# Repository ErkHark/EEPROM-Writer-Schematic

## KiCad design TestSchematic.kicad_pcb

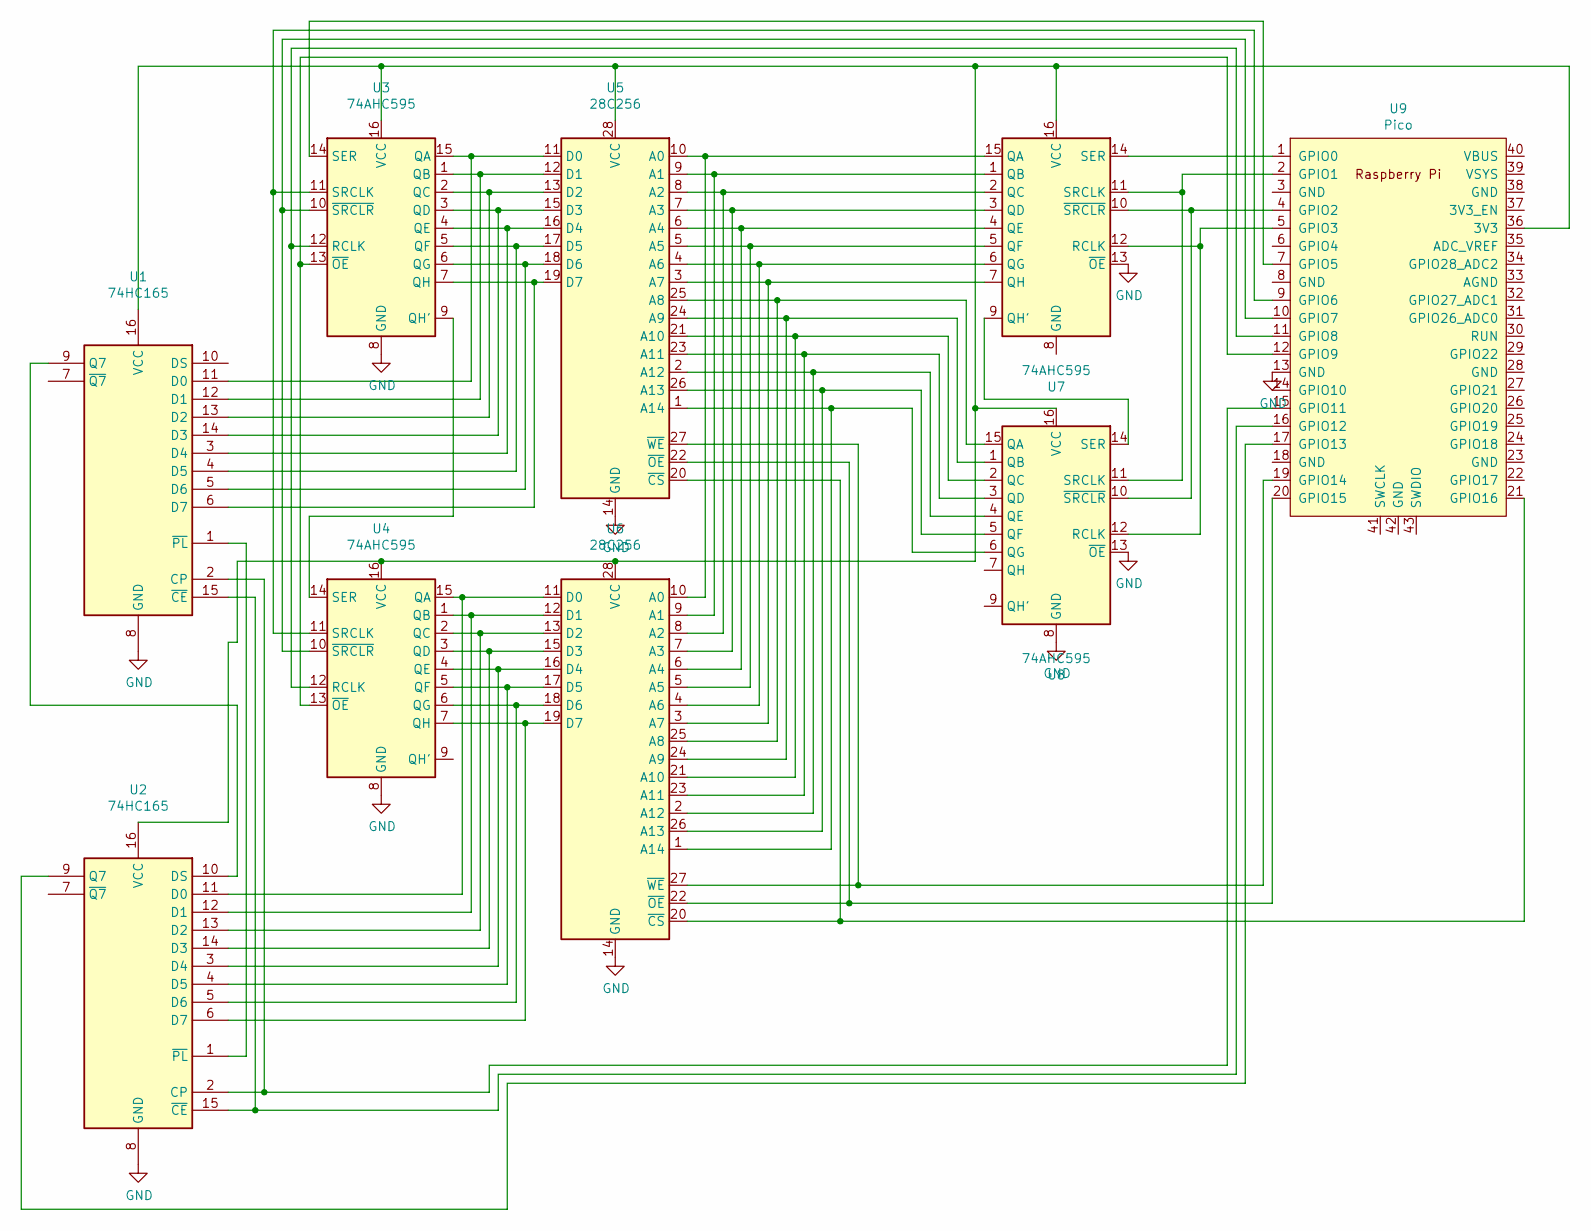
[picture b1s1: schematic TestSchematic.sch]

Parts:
U1, U2: 74HC165; DIP-16_W7.62mm_Socket
U3, U4, U7, U8: 74AHC595; DIP-16_W7.62mm_Socket
U5, U6: 28C256; DIP-28_W15.24mm
U9: Pico; RPi_Pico_SMD_TH

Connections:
unnamed: U1.1 (~PL), U2.1 (~PL)
unnamed: U1.2 (CP), U2.2 (CP), U9.15 (GPIO11)
unnamed: U1.3 (D4), U3.4 (QE), U5.16 (D4)
unnamed: U1.4 (D5), U3.5 (QF), U5.17 (D5)
unnamed: U1.5 (D6), U3.6 (QG), U5.18 (D6)
unnamed: U1.6 (D7), U3.7 (QH), U5.19 (D7)
unnamed: U1.8 (GND), U2.8 (GND), U3.8 (GND), U4.8 (GND), U5.14 (GND), U6.14 (GND), U7.8 (GND), U7.13 (~OE), U8.8 (GND), U8.13 (~OE), U9.13 (GND)
unnamed: U1.9 (Q7), U2.10 (DS)
unnamed: U1.11 (D0), U3.15 (QA), U5.11 (D0)
unnamed: U1.12 (D1), U3.1 (QB), U5.12 (D1)
unnamed: U1.13 (D2), U3.2 (QC), U5.13 (D2)
unnamed: U1.14 (D3), U3.3 (QD), U5.15 (D3)
unnamed: U1.15 (~CE), U2.15 (~CE), U9.16 (GPIO12)
unnamed: U1.16 (VCC), U2.16 (VCC), U3.16 (VCC), U4.16 (VCC), U5.28 (VCC), U6.28 (VCC), U7.16 (VCC), U8.16 (VCC), U9.36 (3V3)
unnamed: U2.3 (D4), U4.4 (QE), U6.16 (D4)
unnamed: U2.4 (D5), U4.5 (QF), U6.17 (D5)
unnamed: U2.5 (D6), U4.6 (QG), U6.18 (D6)
unnamed: U2.6 (D7), U4.7 (QH), U6.19 (D7)
unnamed: U2.9 (Q7), U9.17 (GPIO13)
unnamed: U2.11 (D0), U4.15 (QA), U6.11 (D0)
unnamed: U2.12 (D1), U4.1 (QB), U6.12 (D1)
unnamed: U2.13 (D2), U4.2 (QC), U6.13 (D2)
unnamed: U2.14 (D3), U4.3 (QD), U6.15 (D3)
unnamed: U3.9 (QH'), U4.14 (SER)
unnamed: U3.10 (~SRCLR), U4.10 (~SRCLR), U9.10 (GPIO7)
unnamed: U3.11 (SRCLK), U4.11 (SRCLK), U9.9 (GPIO6)
unnamed: U3.12 (RCLK), U4.12 (RCLK), U9.11 (GPIO8)
unnamed: U3.13 (~OE), U4.13 (~OE), U9.12 (GPIO9)
unnamed: U3.14 (SER), U9.7 (GPIO5)
unnamed: U5.1 (A14), U6.1 (A14), U8.6 (QG)
unnamed: U5.2 (A12), U6.2 (A12), U8.4 (QE)
unnamed: U5.3 (A7), U6.3 (A7), U7.7 (QH)
unnamed: U5.4 (A6), U6.4 (A6), U7.6 (QG)
unnamed: U5.5 (A5), U6.5 (A5), U7.5 (QF)
unnamed: U5.6 (A4), U6.6 (A4), U7.4 (QE)
unnamed: U5.7 (A3), U6.7 (A3), U7.3 (QD)
unnamed: U5.8 (A2), U6.8 (A2), U7.2 (QC)
unnamed: U5.9 (A1), U6.9 (A1), U7.1 (QB)
unnamed: U5.10 (A0), U6.10 (A0), U7.15 (QA)
unnamed: U5.20 (~CS), U6.20 (~CS), U9.21 (GPIO16)
unnamed: U5.21 (A10), U6.21 (A10), U8.2 (QC)
unnamed: U5.22 (~OE), U6.22 (~OE), U9.20 (GPIO15)
unnamed: U5.23 (A11), U6.23 (A11), U8.3 (QD)
unnamed: U5.24 (A9), U6.24 (A9), U8.1 (QB)
unnamed: U5.25 (A8), U6.25 (A8), U8.15 (QA)
unnamed: U5.26 (A13), U6.26 (A13), U8.5 (QF)
unnamed: U5.27 (~WE), U6.27 (~WE), U9.19 (GPIO14)
unnamed: U7.9 (QH'), U8.14 (SER)
unnamed: U7.10 (~SRCLR), U8.10 (~SRCLR), U9.4 (GPIO2)
unnamed: U7.11 (SRCLK), U8.11 (SRCLK), U9.2 (GPIO1)
unnamed: U7.12 (RCLK), U8.12 (RCLK), U9.5 (GPIO3)
unnamed: U7.14 (SER), U9.1 (GPIO0)

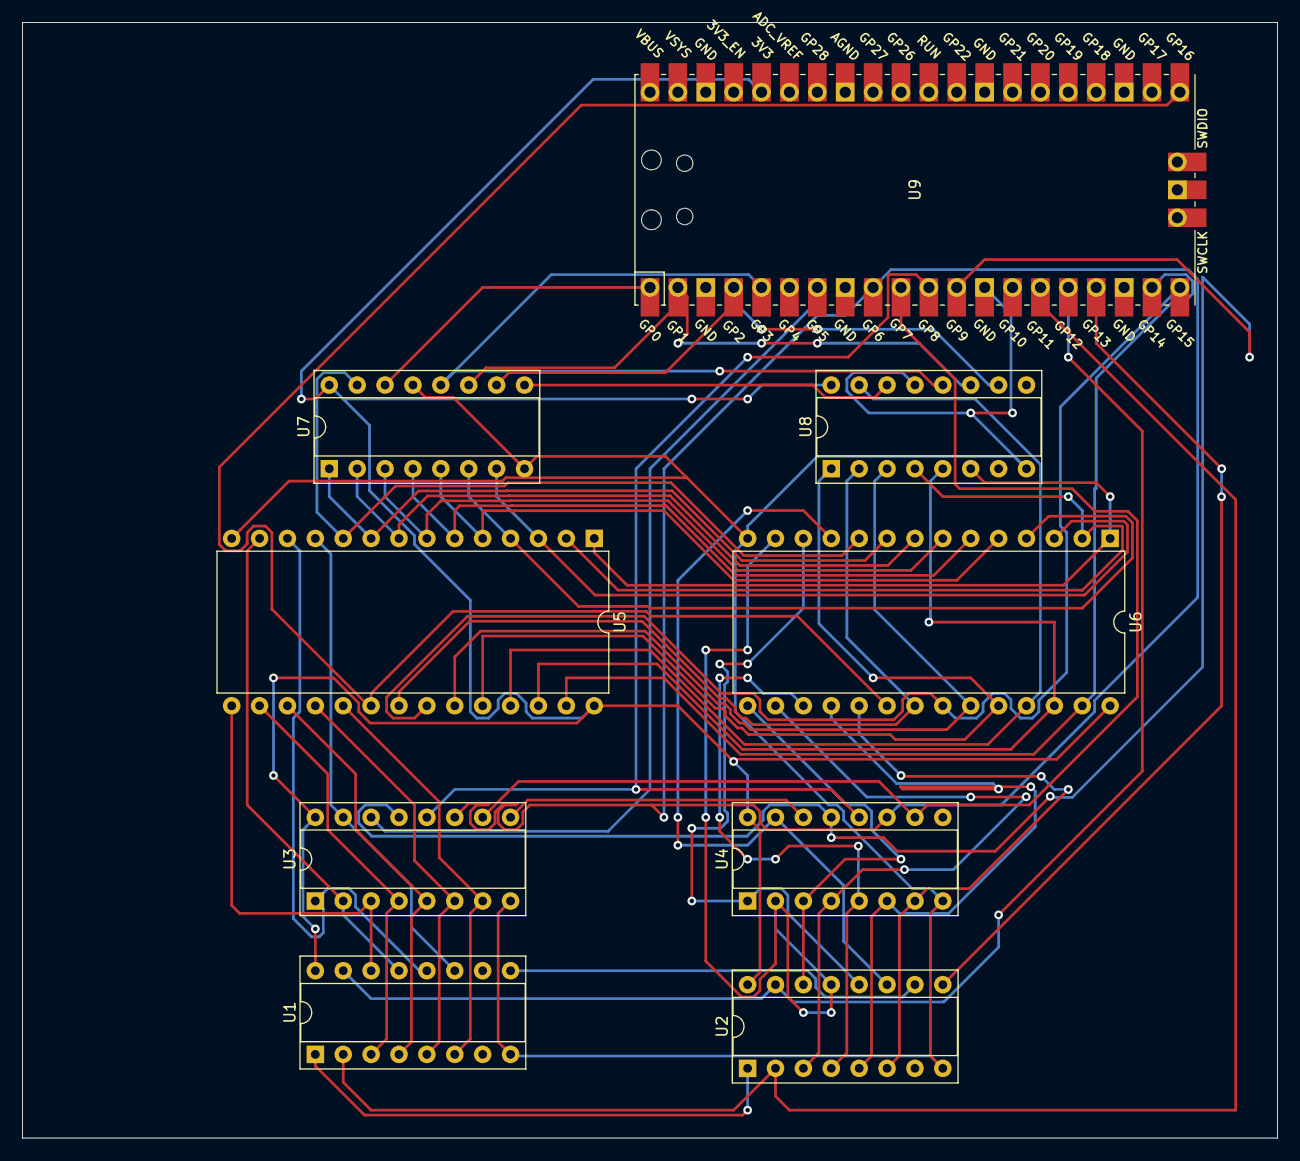
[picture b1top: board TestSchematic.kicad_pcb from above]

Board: 2 copper layers, 114.3 x 101.6 mm, 9 parts (0 on the bottom side), 52 nets.
